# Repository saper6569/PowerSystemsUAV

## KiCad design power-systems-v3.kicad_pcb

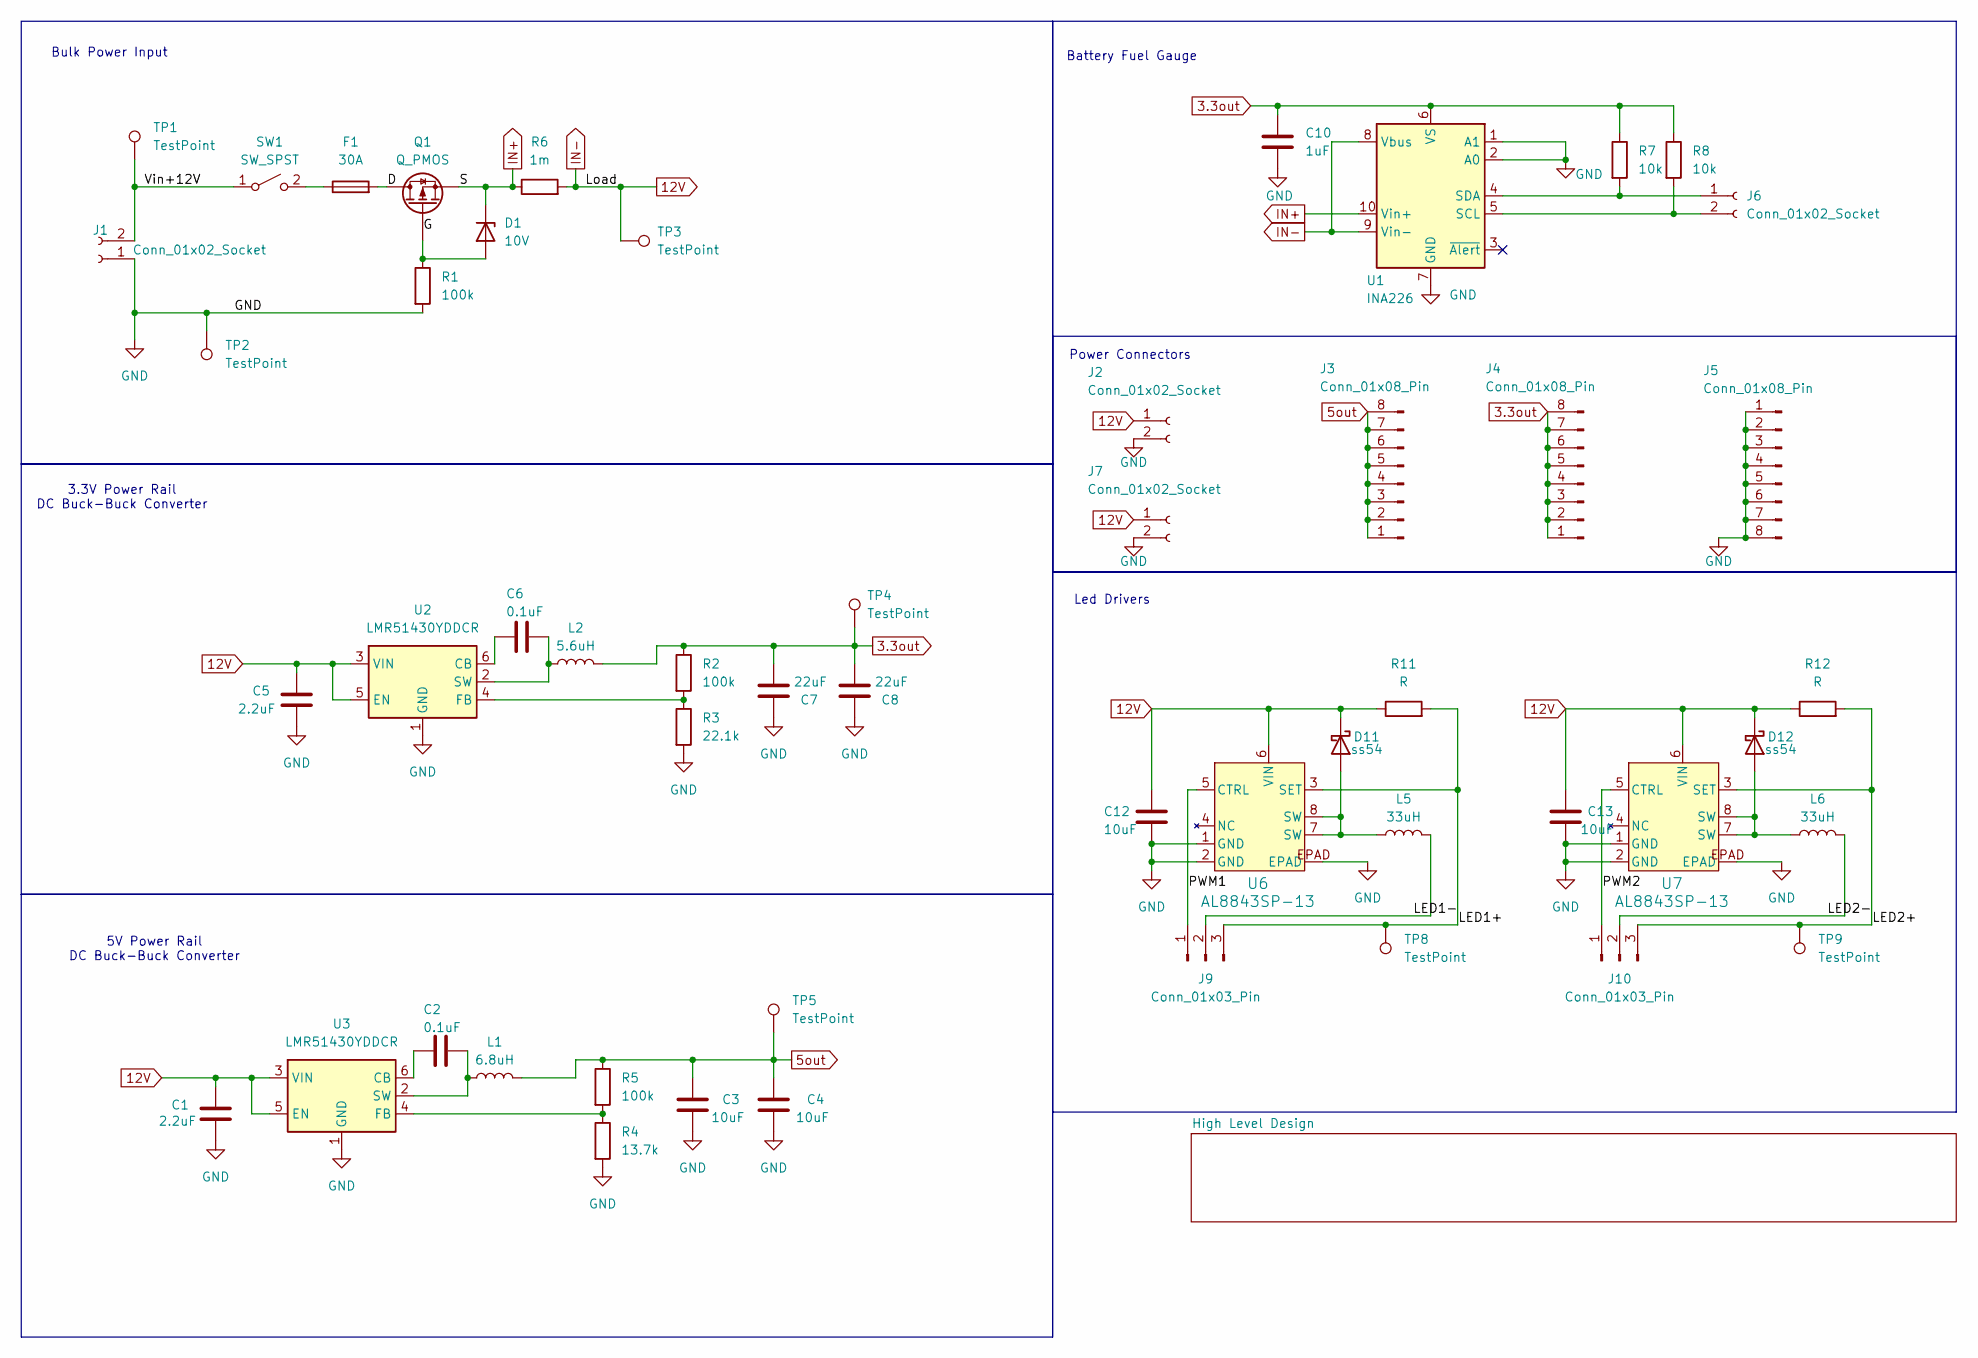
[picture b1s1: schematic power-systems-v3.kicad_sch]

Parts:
C1, C5: 2.2uF; C_0603_1608Metric_Pad1.08x0.95mm_HandSolder
C2, C6: 0.1uF; C_0603_1608Metric_Pad1.08x0.95mm_HandSolder
C3, C4, C12, C13: 10uF; CP_Elec_4x5.4
C7, C8: 22uF; C_1206_3216Metric_Pad1.33x1.80mm_HandSolder
C10: 1uF; CP_Elec_4x5.4
D1: 10V; D_SMB_Handsoldering
D11, D12: ss54; D_SMA
F1: 30A; FuseHolder
J1, J2, J7: Conn_01x02_Socket; AMASS_XT60-F_1x02_P7.20mm_Vertical
J3, J4, J5: Conn_01x08_Pin; PinHeader_1x08_P2.54mm_Vertical
J6: Conn_01x02_Socket; PinHeader_1x02_P2.54mm_Vertical
J9, J10: Conn_01x03_Pin; PinHeader_1x03_P2.54mm_Vertical
L1: 6.8uH
L2: 5.6uH
L5, L6: 33uH
Q1: Q_PMOS; TO-220-3_Vertical
R1, R2, R5: 100k; R_0603_1608Metric_Pad0.98x0.95mm_HandSolder
R3: 22.1k; R_0603_1608Metric_Pad0.98x0.95mm_HandSolder
R4: 13.7k; C_0805_2012Metric_Pad1.18x1.45mm_HandSolder
R6: 1m; R_1206_3216Metric
R7, R8: 10k; R_0805_2012Metric
R11, R12: R; C_1206_3216Metric
SW1: SW_SPST; switch
TP1, TP2, TP3, TP4, TP5, TP8, TP9: TestPoint; TestPoint_Pad_D2.5mm
U1: INA226; TSSOP-10_3x3mm_P0.5mm
U2, U3: LMR51430YDDCR; SOT-23-6
U6, U7: AL8843SP-13; SO8_AL8843SP-13_DIO-M

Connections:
3.3out: C7.2, C8.2, C10.1, J4.1, J4.2, J4.3, J4.4, J4.5, J4.6, J4.7, J4.8, L2.2, R2.1, R7.1, R8.1, TP4.1 (1_1), U1.6 (VS)
5out: C3.1, C4.1, J3.1, J3.2, J3.3, J3.4, J3.5, J3.6, J3.7, J3.8, L1.2, R5.1, TP5.1 (1_1)
12V: C1.1, C5.1, C12.1, C13.1, D11.1 (K), D12.1 (K), J2.1, J7.1, R6.2, R11.1, R12.1, TP3.1 (1_1), U1.8 (Vbus), U1.9 (Vin-), U2.3 (VIN), U2.5 (EN), U3.3 (VIN), U3.5 (EN), U6.6 (VIN), U7.6 (VIN)
/D: F1.2, Q1.2 (D)
/LED1+: J9.3, R11.2, TP8.1 (1_1), U6.3 (SET)
/LED1-: J9.2, L5.2
/LED2+: J10.3, R12.2, TP9.1 (1_1), U7.3 (SET)
/LED2-: J10.2, L6.2
/PWM1: J9.1, U6.5 (CTRL)
/PWM2: J10.1, U7.5 (CTRL)
/Vin+12V: J1.2, SW1.1 (A), TP1.1 (1_1)
GND: C1.2, C3.2, C4.2, C5.2, C7.1, C8.1, C10.2, C12.2, C13.2, J1.1, J2.2, J5.1, J5.2, J5.3, J5.4, J5.5, J5.6, J5.7, J5.8, J7.2, R1.2, R3.2, R4.2, TP2.1 (1_1), U1.1 (A1), U1.2 (A0), U1.7 (GND), U2.1 (GND), U3.1 (GND), U6.1 (GND), U6.2 (GND), U6.EPAD, U7.1 (GND), U7.2 (GND), U7.EPAD
IN+: D1.1 (K), Q1.3 (S), R6.1, U1.10 (Vin+)
unnamed: D1.2 (A), Q1.1 (G), R1.1
unnamed: D11.2 (A), L5.1, U6.7 (SW), U6.8 (SW)
unnamed: D12.2 (A), L6.1, U7.7 (SW), U7.8 (SW)
unnamed: J6.1, R7.2, U1.4 (SDA)
unnamed: J6.2, R8.2, U1.5 (SCL)
unnamed: F1.1, SW1.2 (B)
unnamed: C6.2, U2.6 (CB)
unnamed: R2.2, R3.1, U2.4 (FB)
unnamed: C6.1, L2.1, U2.2 (SW)
unnamed: C2.2, U3.6 (CB)
unnamed: R4.1, R5.2, U3.4 (FB)
unnamed: C2.1, L1.1, U3.2 (SW)

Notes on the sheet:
Battery Fuel Gauge
Led Drivers
3.3V Power Rail DC Buck-Buck Converter
5V Power Rail DC Buck-Buck Converter
Bulk Power Input
Power Connectors

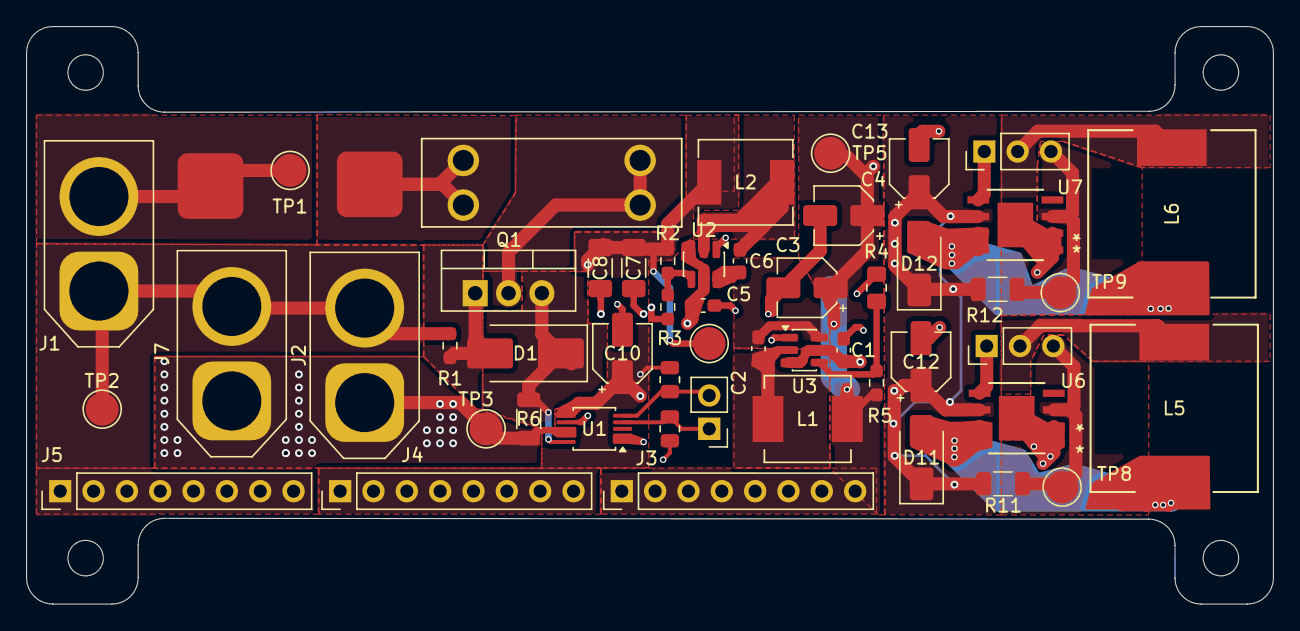
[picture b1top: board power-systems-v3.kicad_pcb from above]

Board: 4 copper layers, 95.0 x 44.0 mm, 52 parts (0 on the bottom side), 25 nets.
